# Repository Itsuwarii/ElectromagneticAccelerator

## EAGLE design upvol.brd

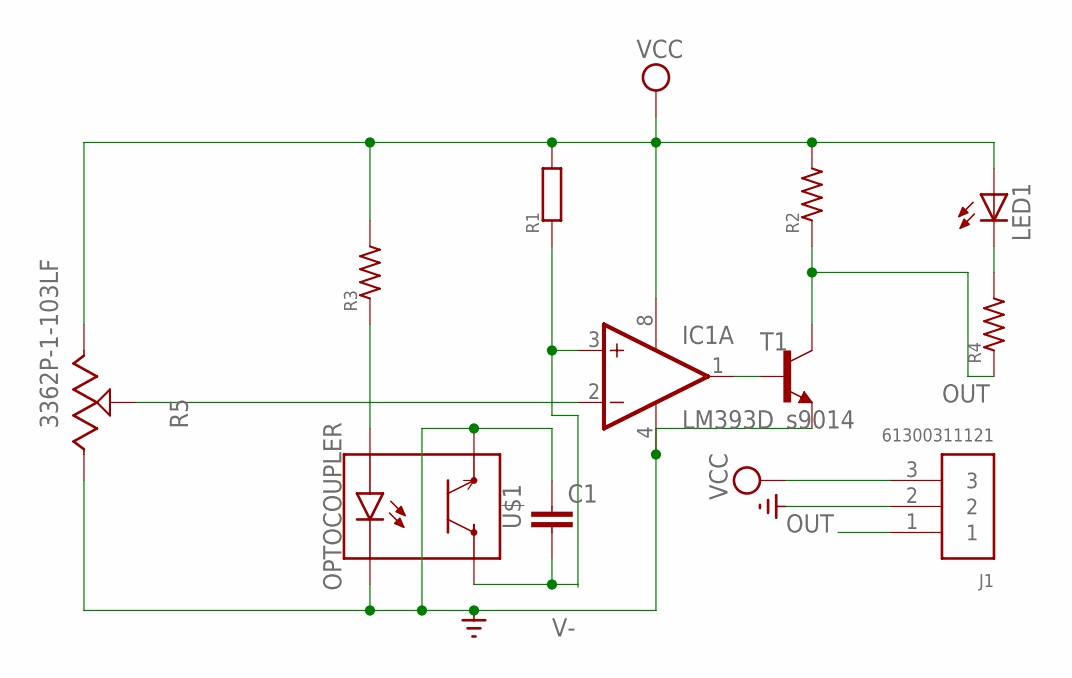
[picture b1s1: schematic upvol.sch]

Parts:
C1: C2.5/2; C2.5-2
IC1: LM393D; SO08
J1: 61300311121
LED1: LED3MM
R1: 10K; 0204V
R2, R4: 10K; RC-MASTER-SMD_R0603MP
R3: 4.7k; RC-MASTER-SMD_R0603MP
R5: 3362P-1-103LF
T1: s9014; SOT23-EBC
U$1: OPTOCOUPLER

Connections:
unnamed: C1.2, IC1.3 (+IN), R1.1, U$1.C
unnamed: R3.1, U$1.A
unnamed: LED1.K (C), R4.2
unnamed: IC1.2 (-IN), R5.2
unnamed: IC1.1 (OUT), T1.B
OUT: J1.1, R2.1, R4.1, T1.C
V+: IC1.8 (V+), J1.3, LED1.A, R1.2, R2.2, R3.2, R5.1
V-: C1.1, IC1.4 (V-), J1.2, R5.3, T1.E, U$1.E, U$1.K

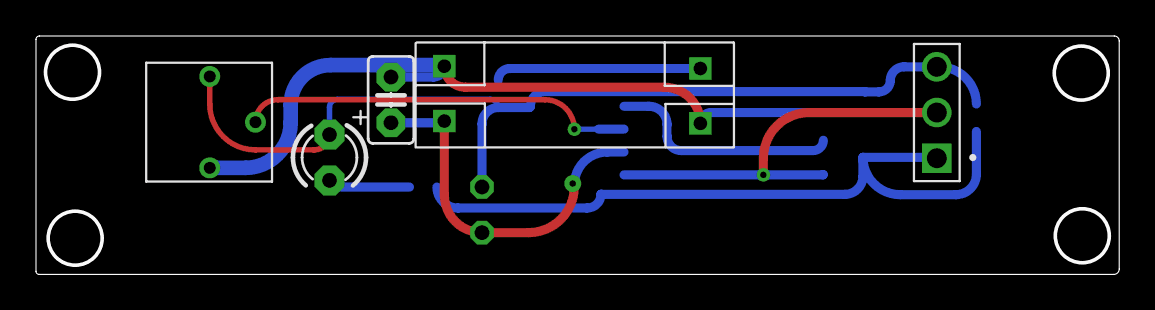
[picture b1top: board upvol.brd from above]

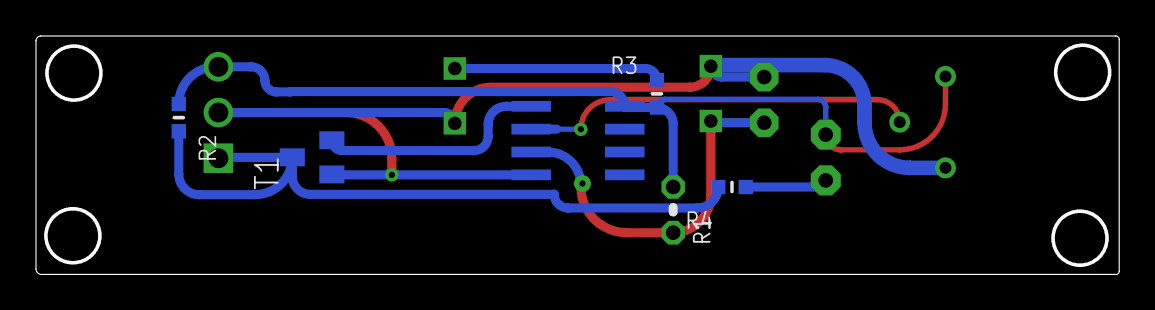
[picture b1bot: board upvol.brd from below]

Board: 2 copper layers, 60.0 x 13.0 mm, 11 parts (6 on the bottom side), 8 nets.

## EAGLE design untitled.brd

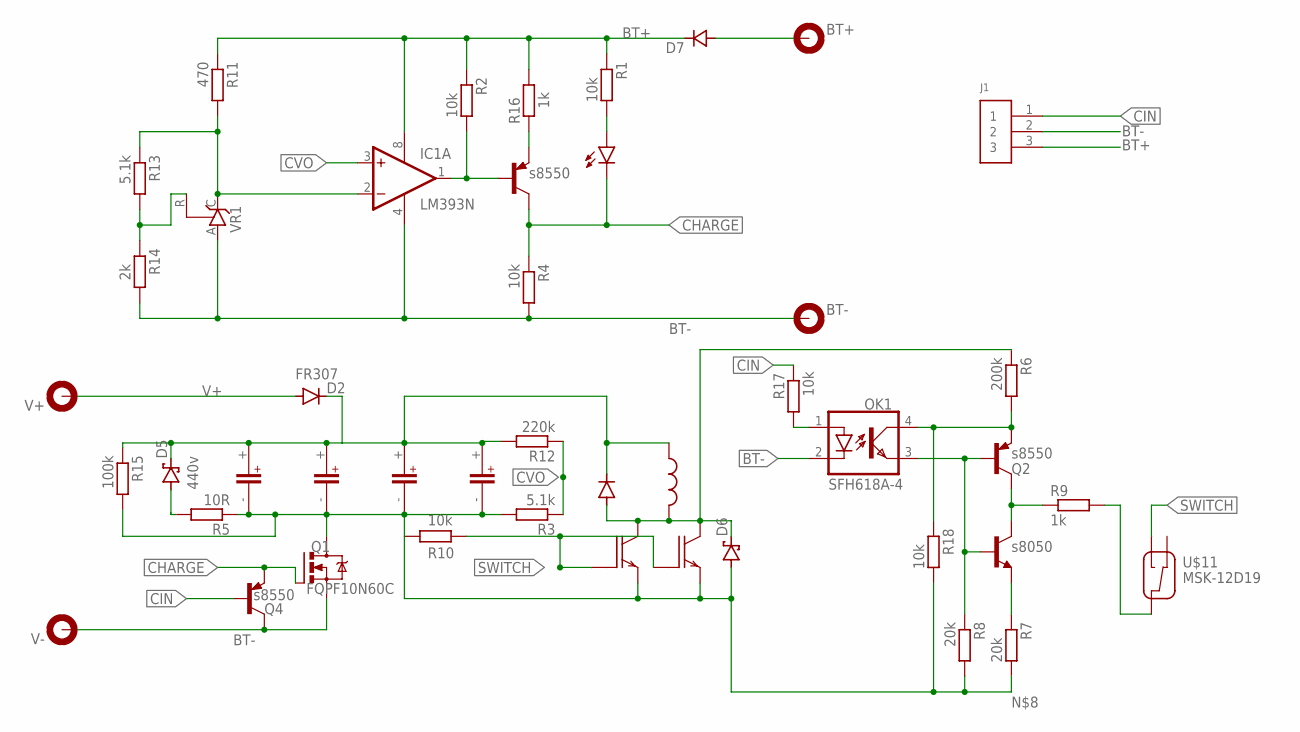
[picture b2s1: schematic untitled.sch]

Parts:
BT+: MOUNT-PAD-ROUND3.0; 3,0-PAD
BT-: MOUNT-PAD-ROUND3.0; 3,0-PAD
D1: SB320; DO201-15
D2: FR307; DO15-12
D5: 440v; E2LINE
D6: DS_E2L; E2LINE
D7: D_E2L; E2LINE
IC1: LM393N; DIL08
J1: 61300311121
LED1: TLLY4400; LED3MM
OK1: SFH618A-4; DIP4
Q1: FQPF10N60C; TO220BV
Q2, Q3, Q4: s8550; TO92
R1, R2, R4, R10, R17, R18: 10k; 0207/2V
R3, R13: 5.1k; 0207/2V
R5: 10R; 0207/2V
R6: 200k; 0207/2V
R7, R8: 20k; 0207/2V
R9: 1k; 0309/12
R11: 470; 0207/2V
R12: 220k; 0207/2V
R14: 2k; 0207/2V
R15: 100k; 0207/2V
R16: 1k; 0207/2V
T3: s8050; TO92
U$1, U$2, U$3, U$4: RUBYCON_450V_270UF; RUBYCON_22*40
U$6: COIL-301025; 30*10*25
U$9, U$13: IGBT-N-TO247; TO-247AD-V
U$11: MSK-12D19; 12D19
V+: MOUNT-PAD-ROUND3.0; 3,0-PAD
V-: MOUNT-PAD-ROUND3.0; 3,0-PAD
VR1: TL431CLP; TO92-CLP

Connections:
BT+: D7.1 (C), IC1.8 (V+), J1.3, R1.1, R2.1, R11.1, R16.2
BT-: BT-.B3,0, IC1.4 (V-), J1.2, OK1.2 (C), Q1.S, Q4.1 (C), R4.2, R14.2, V-.B3,0, VR1.A
CHARGE: LED1.K (C), Q1.G, Q3.1 (C), Q4.3 (E), R4.1
CIN: J1.1, Q4.2 (B), R17.2
CVO: IC1.3 (+IN), R3.1, R12.1
unnamed: IC1.1 (OUT), Q3.2 (B), R2.2
unnamed: BT+.B3,0, D7.2 (A)
unnamed: D5.2 (A), R5.2
unnamed: D1.A, D6.1 (K), R6.1, U$6.P$2 (2), U$9.C, U$13.C
unnamed: IC1.2 (-IN), R11.2, R13.1, VR1.C
unnamed: LED1.A, R1.2
unnamed: R13.2, R14.1, VR1.R
unnamed: D6.2 (A), Q1.D, R3.2, R5.1, R7.2, R8.2, R10.1, R15.2, R18.2, U$1.-, U$2.-, U$3.-, U$4.-, U$9.E, U$13.E
unnamed: Q2.1 (C), R9.1, T3.2 (C)
unnamed: Q3.3 (E), R16.1
unnamed: OK1.4 (COL), Q2.3 (E), R6.2, R18.1
unnamed: OK1.1 (A), R17.1
unnamed: R7.1, T3.3 (E)
unnamed: OK1.3 (EMIT), Q2.2 (B), R8.1, T3.1 (B)
unnamed: R9.2, U$11.COM
SWITCH: R10.2, U$9.G, U$11.NO, U$13.G
UC: D1.C, D2.C, D5.1 (K), R12.2, R15.1, U$1.+, U$2.+, U$3.+, U$4.+, U$6.P$1 (1)
V+: D2.A, V+.B3,0

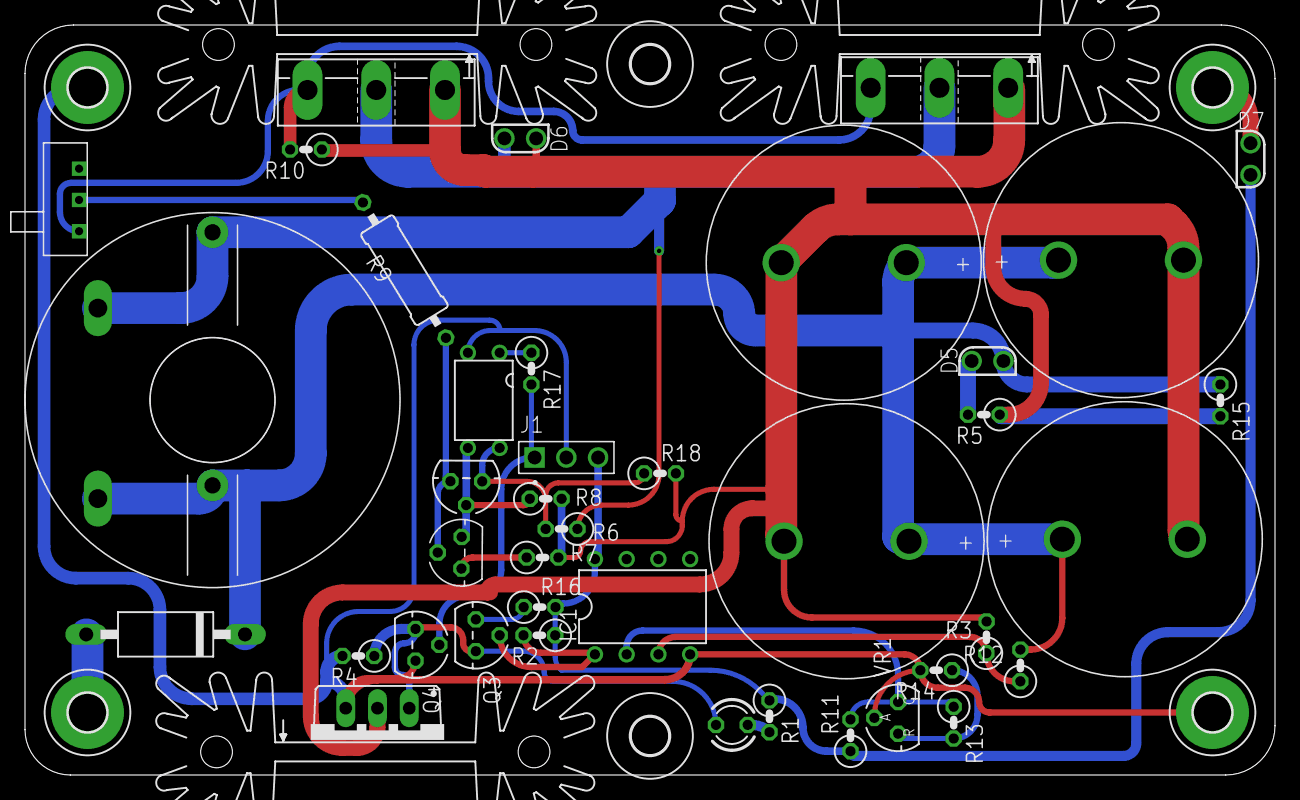
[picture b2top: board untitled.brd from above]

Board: 2 copper layers, 99.9 x 59.9 mm, 50 parts (1 on the bottom side), 23 nets.

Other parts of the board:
U$5, U$10, U$14: SK104
U$7, U$8: 3,0

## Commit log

2021-10-08 add readme
2021-12-23 更新输入模块
